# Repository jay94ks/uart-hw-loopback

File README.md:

## UART hardware loopback.
This hardware causes `UART` to loop back at the hardware level.
Developed based on the `STM32F042` and `CH340` chips, 
it taps the serial communication of the target software 
using the `baud-rate` auto-negotiation function of `VCP`.

In addition, since the pins of the 'SL2.1A' chip are left, 
so I added the USB hub function to utilize them.
and 'PD (Power Delivery)' input in case the current is insufficient.

### Hardware:

### Schematic:

## How to connect:
### Requirements:
1. UART hardware loopback board with `USB Type-C` cable.
2. Target hardware and software.
3. This tapping software.

### Steps to configure the hardware:
1. Connect the data cable, `USB Type-C` to your PC,
2. Attach a `COM` port of `F042VCP` to target software.
3. Then, attach a `COM` port of `CH340` to this tapping software.
4. And, configure this tapping software to communicate with the target hardware.

## Flashing the firmware:
~~This board's `SL2.1A` USB hub chip seems like that disable the SWD pins.
(This seems to be a problem that occurs when the DP/DM pins wired on the board activate DFU mode or probe-like something)~~
So, you can flash the `F042F6P6` chip like:

### Set-up pull resistor to `BOOT0`.
This enables `ST-Link` SWD pins. if `BOOT0` pin is floating, the chip will never enable `DFU` or `SWD` pins.
* `BOOT0` -> pull down: enables `SWD`.
* `BOOT0` -> pull up: enables `DFU`.

### Using development board prototype.
Solder the `F042F6P6` chip to development board or use non-solder programming tools, and flash your chip, then re-solder it to this board. 

### `USB DFU` mode.
Initially, the `F042F6P6` chip will be booted in DFU mode.

1. download `DfuSe` tool from ST microelectronics website:
    https://www.st.com/content/my_st_com/en/products/development-tools/software-development-tools/stm32-software-development-tools/stm32-programmers/stsw-stm32080.license=1635064983409.product=STSW-STM32080.version=3.0.6.html#get-software

2. install it and goto `[System drive]:\Program Files (x86)\STMicroelectronics\Software\DfuSe v3.0.6\Bin` using explorer.

3. double click `DfuFileMgr.exe`
4. check first option, `I want to GENERATE a DFU file from S19, HEX or BIN files` then click `next`.
5. put `DF11` to `Product ID` field.
6. click `S19 or Hex...` button then, select your built `HEX` file, and click `Generate`.
7. close `DFU File Manager` tool, and double click `DfuSeDemo.exe` file.
8. select `STM device in DFU mode` from `Available DFU Devices` combo box.
9. click `Choose...` button on `Upgrade or Verify Action` panel.
10. select `DFU` file that generated at 6th process, then click `Upgrade`.
11. finally, click `Leave DFU mode` on `Available DFU Devices` panel.
12. unplug your board and re-plug it.
13. done.

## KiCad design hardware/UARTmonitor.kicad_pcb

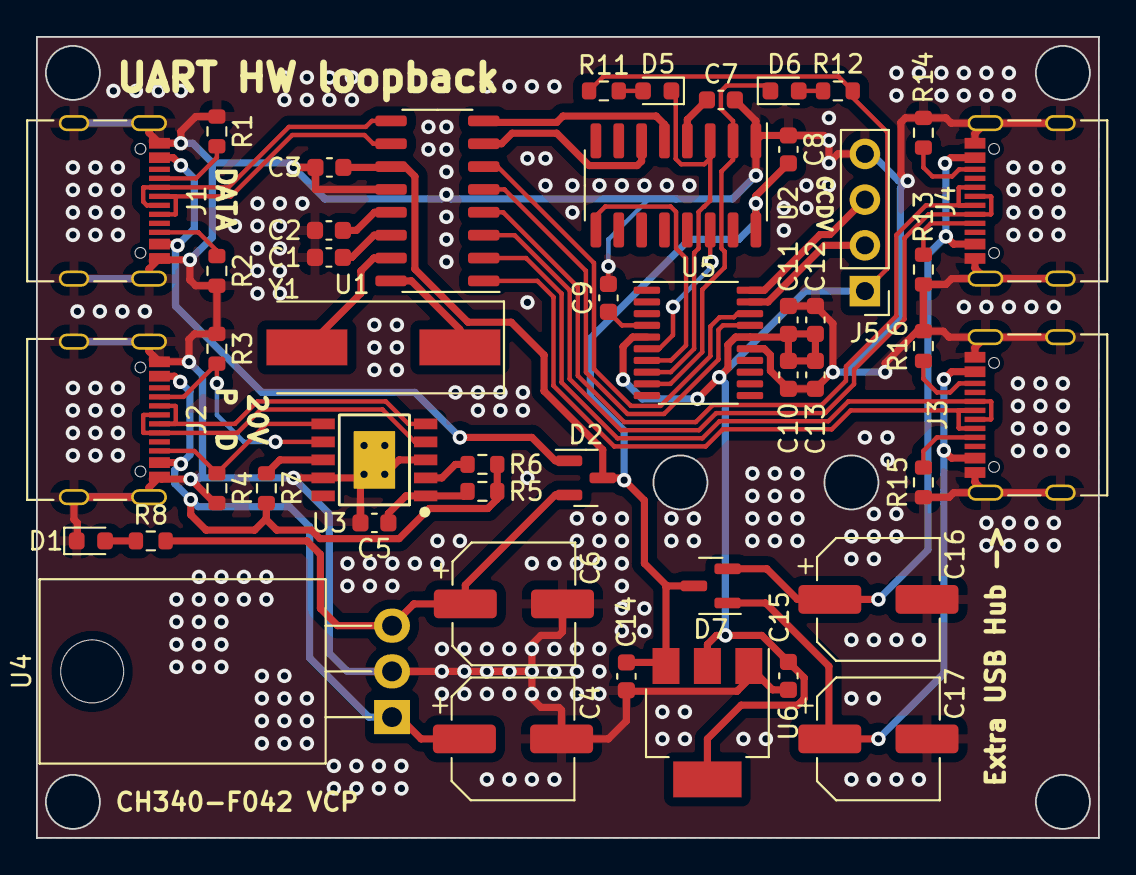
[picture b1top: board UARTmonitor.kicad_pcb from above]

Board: 2 copper layers, 59.0 x 44.5 mm, 48 parts (0 on the bottom side), 46 nets.

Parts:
C1, C2, C3, C14, C15: 10uF; C_0603_1608Metric
C4, C6, C16, C17: 100uF/25V; CP_Elec_6.3x7.7
C5: 1uF; C_0603_1608Metric
C7, C8, C9, C10, C11, C12, C13: 100nF; C_0603_1608Metric
D1, D5, D6: LED; LED_0603_1608Metric
D2: BAT54C; SOT-23
D7: BAT54A; SOT-23
J1: USB_DATA; USB_C_Receptacle_Palconn_UTC16-G
J2: USB_PD; USB_C_Receptacle_Palconn_UTC16-G
J3: USB_EXTRA2; USB_C_Receptacle_Palconn_UTC16-G
J4: USB_EXTRA1; USB_C_Receptacle_Palconn_UTC16-G
J5: Conn_01x04; PinHeader_1x04_P2.54mm_Vertical
R1, R2, R3, R4, R13, R14, R15, R16: 5.1k; R_0603_1608Metric
R5, R8, R11, R12: 1k; R_0603_1608Metric
R6, R7: 10k; R_0603_1608Metric
U1: SL2.1A; SO-16_3.9x9.9mm_P1.27mm
U2: CH340C; SOIC-16_3.9x9.9mm_P1.27mm
U3: CH224K; ESSOP-10_CH224K
U4: LM7805_TO220; TO-220-3_Horizontal_TabDown
U5: STM32F042F6P6; TSSOP-20_4.4x6.5mm_P0.65mm
U6: AMS1117-3.3; SOT-223-3_TabPin2
Y1: 12MHz; Crystal_SMD_HC49-SD

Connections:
+3V3: C10.1, C11.1, C12.2, C13.1, C15.1, J5.1, R11.1, R12.1, U5.5 (VDDA), U5.16 (VDD), U6.2 (VO)
+5V: C3.1, C8.2, C14.1, D2.3, D7.3, U1.11 (VDD5), U2.16 (VCC), U6.3 (VI)
/1V8: C1.1, U1.14 (VDD18)
/3V3: C2.1, U1.13 (VDD33)
/CH340_CTS-F042_RTS: U2.9 (~CTS), U5.7 (PA1)
/CH340_DM: U1.7 (DM1), U2.6 (UD-)
/CH340_DP: U1.8 (DP1), U2.5 (UD+)
/CH340_RTS-F042_CTS: U2.14 (~RTS), U5.6 (PA0)
/CH340_RX-F042_TX: D5.1 (K), U2.3 (RXD), U5.8 (PA2)
/CH340_TX-F042_RX: D6.1 (K), U2.2 (TXD), U5.9 (PA3)
/DATA_VBUS: D2.1, J1.A4 (VBUS), J1.A9 (VBUS), J1.B4 (VBUS), J1.B9 (VBUS)
/EXTRA1_5V: C16.1, D7.2, J4.A4 (VBUS), J4.A9 (VBUS), J4.B4 (VBUS), J4.B9 (VBUS)
/EXTRA1_DM: J4.A7 (D-), J4.B7 (D-), U1.3 (DM3)
/EXTRA1_DP: J4.A6 (D+), J4.B6 (D+), U1.4 (DP3)
/EXTRA2_5V: C17.1, D7.1, J3.A4 (VBUS), J3.A9 (VBUS), J3.B4 (VBUS), J3.B9 (VBUS)
/EXTRA2_DM: J3.A7 (D-), J3.B7 (D-), U1.1 (DM4)
/EXTRA2_DP: J3.A6 (D+), J3.B6 (D+), U1.2 (DP4)
/F042_DM: U1.5 (DM2), U5.17 (PA9/PA11)
/F042_DP: U1.6 (DP2), U5.18 (PA10/PA12)
/PD_5V: C6.1, D2.2, R8.2, U4.3 (VO)
/PD_CC1: J2.A5 (CC1), R3.2, U3.7 (CC1)
/PD_CC2: J2.B5 (CC2), R4.1, U3.6 (CC2)
/PD_DM: J2.A7 (D-), J2.B7 (D-), U3.5 (DM)
/PD_DP: J2.A6 (D+), J2.B6 (D+), U3.4 (DP)
/PD_VBUS: C4.1, J2.A4 (VBUS), J2.A9 (VBUS), J2.B4 (VBUS), J2.B9 (VBUS), R5.1, R6.1, R7.2, U4.1 (VI)
/USB_DM: J1.A7 (D-), J1.B7 (D-), U1.9 (DM)
/USB_DP: J1.A6 (D+), J1.B6 (D+), U1.10 (DP)
F042_CLK: J5.3, U5.20 (PA14)
F042_DIO: J5.2, U5.19 (PA13)
GND: C1.2, C2.2, C3.2, C4.2, C5.2, C6.2, C7.2, C8.1, C9.2, C10.2, C11.2, C12.1, C13.2, C14.2, C15.2, C16.2, C17.2, D1.1 (K), J1.A1 (GND), J1.A12 (GND), J1.B1 (GND), J1.B12 (GND), J1.S1 (SHIELD), J2.A1 (GND), J2.A12 (GND), J2.B1 (GND), J2.B12 (GND), J2.S1 (SHIELD), J3.A1 (GND), J3.A12 (GND), J3.B1 (GND), J3.B12 (GND), J3.S1 (SHIELD), J4.A1 (GND), J4.A12 (GND), J4.B1 (GND), J4.B12 (GND), J4.S1 (SHIELD), J5.4, R1.1, R2.2, R3.1, R4.2, R13.1, R14.2, R15.1, R16.2, U1.12 (GND), U2.1 (GND), U3.3 (CFG3), U3.9 (CFG1), U3.11 (GND), U4.2 (GND), U5.15 (VSSA), U6.1 (GND)
unnamed: D1.2 (A), R8.1
unnamed: D5.2 (A), R11.2
unnamed: D6.2 (A), R12.2
unnamed: J1.A5 (CC1), R1.2
unnamed: J1.B5 (CC2), R2.1
unnamed: J3.A5 (CC1), R15.2
unnamed: J3.B5 (CC2), R16.1
unnamed: J4.A5 (CC1), R13.2
unnamed: J4.B5 (CC2), R14.1
unnamed: U1.16 (XIN), Y1.1
unnamed: U1.15 (XOUT), Y1.2
unnamed: C7.1, U2.4 (V3)
unnamed: R6.2, U3.2 (CFG2)
unnamed: R7.1, U3.8 (VBUS)
unnamed: C9.1, U5.4 (NRST)
VDD: C5.1, R5.2, U3.1 (VDD)

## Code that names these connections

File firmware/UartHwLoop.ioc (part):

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Mcu.Name=STM32F042F6Px
Mcu.Package=TSSOP20
Mcu.UserName=STM32F042F6Px
PA0.Mode=CTS_RTS
PA0.Signal=USART2_CTS
PA1.Mode=CTS_RTS
PA1.Signal=USART2_RTS
PA11.Mode=Device
PA11.Signal=USB_DM
PA12.Mode=Device
PA12.Signal=USB_DP
PA13.Mode=Serial_Wire
PA13.Signal=SYS_SWDIO
PA14.Mode=Serial_Wire
PA14.Signal=SYS_SWCLK
PA2.Mode=Asynchronous
PA2.Signal=USART2_TX
PA3.Mode=Asynchronous
PA3.Signal=USART2_RX
RCC.SYSCLKFreq_VALUE=48000000
RCC.SYSCLKSource=RCC_SYSCLKSOURCE_PLLCLK
board=custom

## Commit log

2024-02-27 Firmware done.
2024-02-27 Firmware modified.
